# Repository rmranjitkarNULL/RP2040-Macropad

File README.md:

# RP2040-Macropad
A Macropad made with the KB2040 MCU

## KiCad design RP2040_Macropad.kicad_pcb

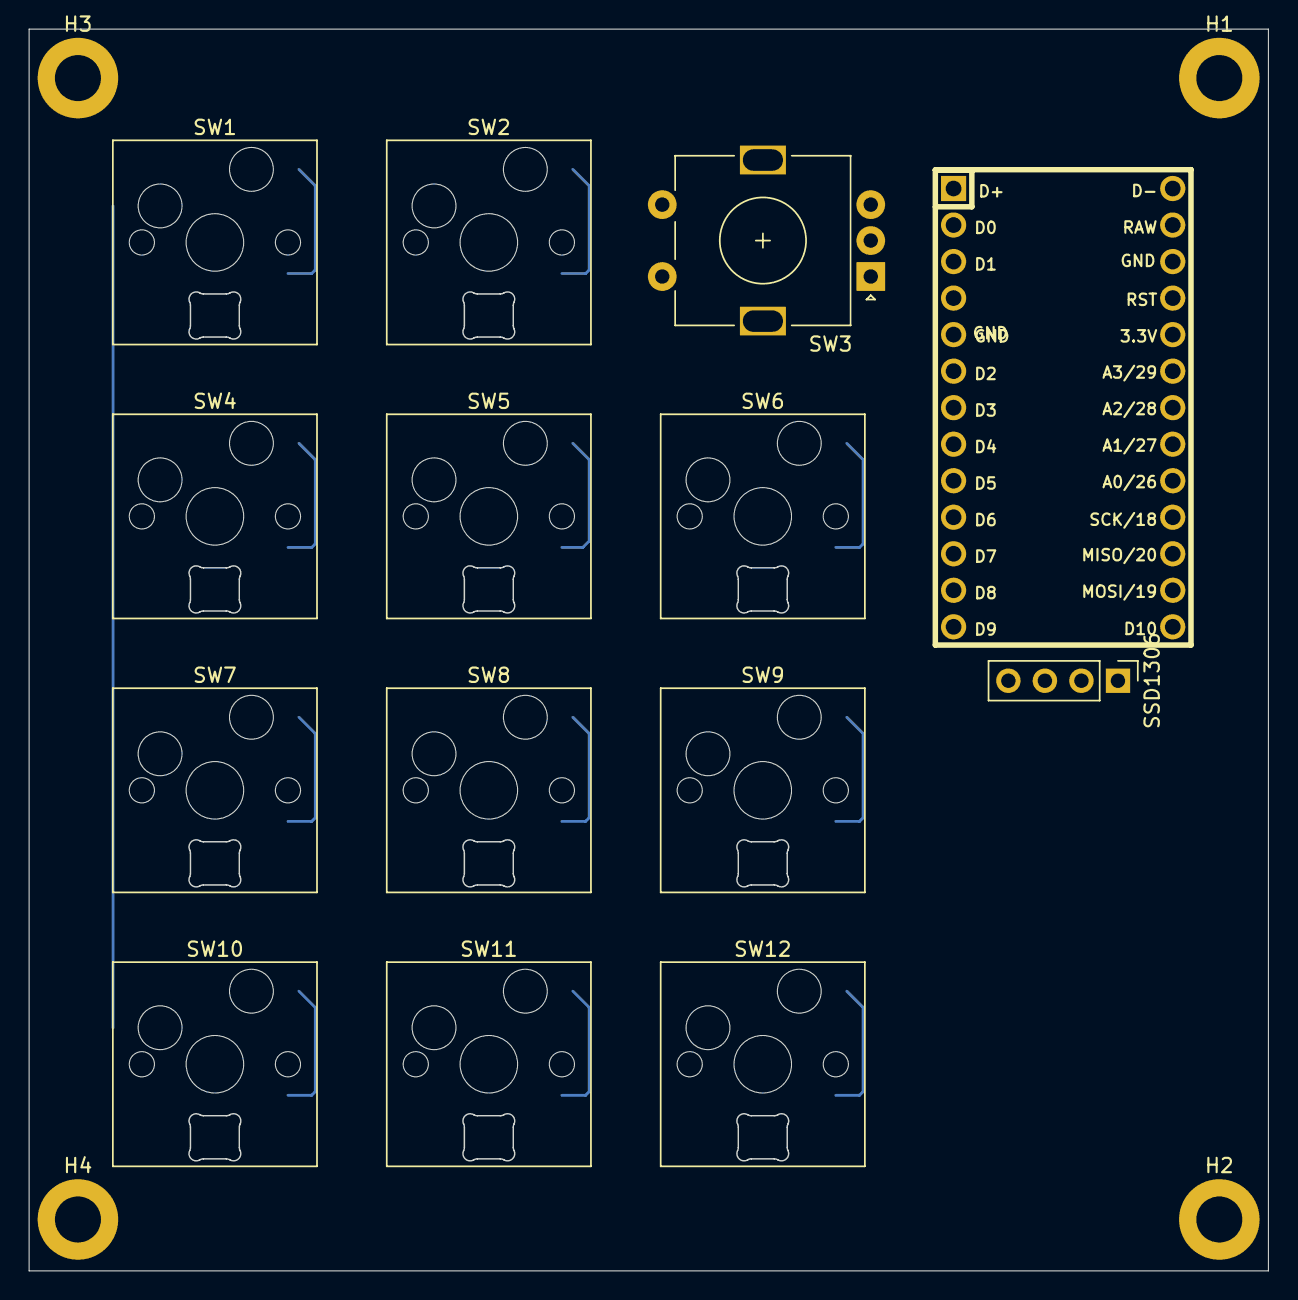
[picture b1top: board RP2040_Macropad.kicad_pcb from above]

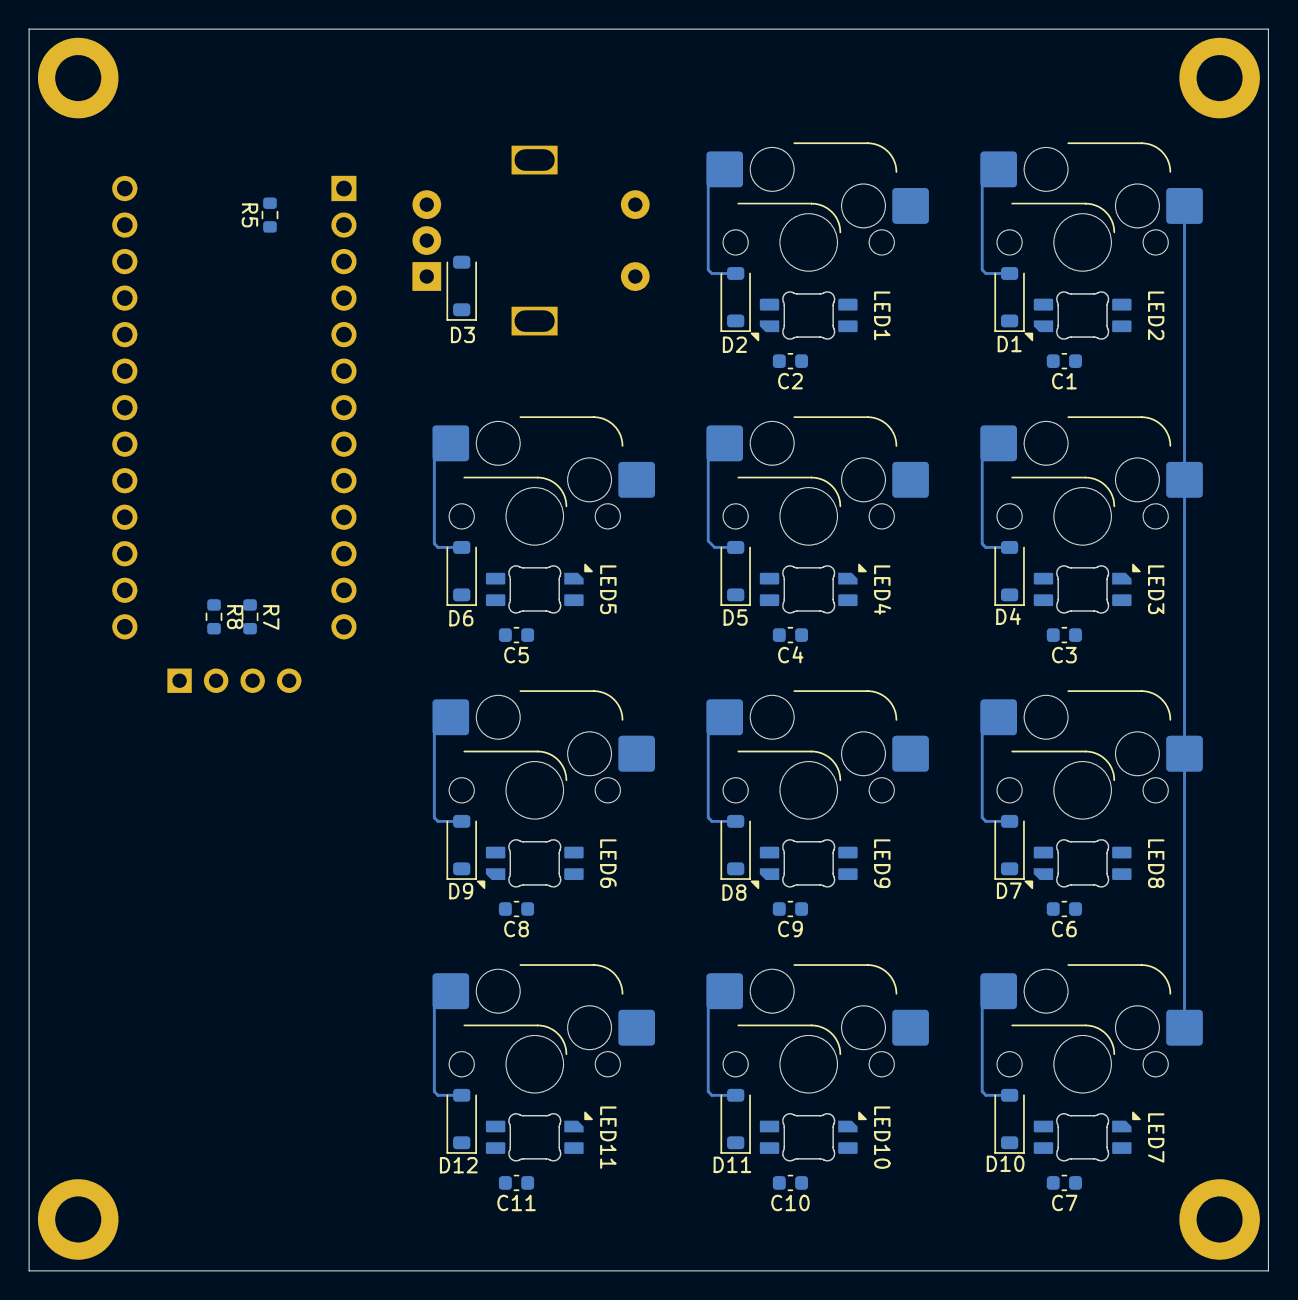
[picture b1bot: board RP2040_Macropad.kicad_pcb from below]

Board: 2 copper layers, 86.2 x 86.4 mm, 55 parts (37 on the bottom side), 35 nets.

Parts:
C1, C2, C3, C4, C5, C6, C7, C8, C9, C10, C11: 100nf; C_0603_1608Metric
D1, D2, D3, D4, D5, D6, D7, D8, D9, D10, D11, D12: 1N4148W; D_SOD-123
H1, H2, H3, H4: MountingHole_Pad; MountingHole_3.2mm_M3_DIN965_Pad
LED1, LED2, LED3, LED4, LED5, LED6, LED7, LED8, LED9, LED10, LED11: MX_SK6812MINI-E; LED_MX_6028R
R5: 330; R_0603_1608Metric
R7, R8: 4k7; R_0603_1608Metric
SSD1306: 128 x 32; PinHeader_1x04_P2.54mm_Vertical
SW1, SW2, SW4, SW5, SW6, SW7, SW8, SW9, SW10, SW11, SW12: SW_Push; SW_Hotswap_Kailh_MX_1.00u
SW3: RotaryEncoder_Switch; RotaryEncoder_Alps_EC11E-Switch_Vertical_H20mm
U1: kb2040

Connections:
+3.3V: C1.2, C2.2, C3.2, C4.2, C5.2, C6.2, C7.2, C8.2, C9.2, C10.2, C11.2, LED1.1 (VDD), LED2.1 (VDD), LED3.1 (VDD), LED4.1 (VDD), LED5.1 (VDD), LED6.1 (VDD), LED7.1 (VDD), LED8.1 (VDD), LED9.1 (VDD), LED10.1 (VDD), LED11.1 (VDD), R7.1, R8.1, SSD1306.3, U1.18 (3.3v)
Col 1: SW1.1, SW4.1, SW7.1, SW10.1, U1.3 (D1)
Col 2: SW2.1, SW5.1, SW8.1, SW11.1, U1.6 (D2)
Col 3: SW3.S1, SW6.1, SW9.1, SW12.1, U1.7 (D3)
GND: C1.1, C2.1, C3.1, C4.1, C5.1, C6.1, C7.1, C8.1, C9.1, C10.1, C11.1, H1.1, H2.1, H3.1, H4.1, LED1.4 (VSS), LED2.4 (VSS), LED3.4 (VSS), LED4.4 (VSS), LED5.4 (VSS), LED6.4 (VSS), LED7.4 (VSS), LED8.4 (VSS), LED9.4 (VSS), LED10.4 (VSS), LED11.4 (VSS), SSD1306.4, SW3.C, U1.4 (GND), U1.5 (GND), U1.16 (GND)
LED_Matrix: R5.1, U1.2 (D0)
unnamed: D1.2 (A), SW1.2
unnamed: D2.2 (A), SW2.2
unnamed: D3.2 (A), SW3.S2
unnamed: D4.2 (A), SW4.2
unnamed: D5.2 (A), SW5.2
unnamed: D6.2 (A), SW6.2
unnamed: D7.2 (A), SW7.2
unnamed: D8.2 (A), SW8.2
unnamed: D9.2 (A), SW9.2
unnamed: D10.2 (A), SW10.2
unnamed: D11.2 (A), SW11.2
unnamed: D12.2 (A), SW12.2
unnamed: LED1.3 (DIN), R5.2
unnamed: LED1.2 (DOUT), LED2.3 (DIN)
unnamed: LED2.2 (DOUT), LED3.3 (DIN)
unnamed: LED3.2 (DOUT), LED4.3 (DIN)
unnamed: LED4.2 (DOUT), LED5.3 (DIN)
unnamed: LED5.2 (DOUT), LED6.3 (DIN)
unnamed: LED6.2 (DOUT), LED9.3 (DIN)
unnamed: LED7.3 (DIN), LED8.2 (DOUT)
unnamed: LED8.3 (DIN), LED9.2 (DOUT)
unnamed: LED7.2 (DOUT), LED10.3 (DIN)
unnamed: LED10.2 (DOUT), LED11.3 (DIN)
Row 1: D1.1 (K), D2.1 (K), D3.1 (K), U1.8 (D4)
Row 2: D4.1 (K), D5.1 (K), D6.1 (K), U1.9 (D5)
Row 3: D7.1 (K), D8.1 (K), D9.1 (K), U1.10 (D6)
Row 4: D10.1 (K), D11.1 (K), D12.1 (K), U1.11 (D7)
SCL_OLED: R8.2, SSD1306.2, U1.19 (A3/29)
SDA_OLED: R7.2, SSD1306.1, U1.20 (A2/28)

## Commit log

2025-11-20 Finished part of the schematic
2025-11-22 Finished schematic, doing layout
2025-11-24 layout complete
